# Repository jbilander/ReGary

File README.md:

# Fat ReGary
A drop in replacement PCB for the Fat Gary chip 

This is WORK IN PROGRESS. If you generate gerbers and order PCBs from this source you are doing so completely at your own risk!.

***

***

***

BOM Rev. 1A
---------
Reference  | Name/Value   | Package | Notes
-|-|-|-|
U1 | GW1N-UV1P5LQ100  | TQFP-100_14x14mm_P0.5mm | Gowin FPGA [GW1N-UV1P5LQ100](https://www.mouser.com/ProductDetail/192-GW1P5LQ100C6-I5)
U2 | LM1117-3.3 | SOT-223 | Low-Dropout Linear Regulator 3.3 Volt
U3 | S-1132B43-M5T1U <br />or <br />TPS73643DBVR | SOT-23-5 | Low-Dropout Linear Regulator 4.3 Volt <br /> [S-1132B43-M5T1U](https://www.mouser.com/ProductDetail/628-S-1132B43-M5T1G) <br /> [TPS73643DBVR](https://www.mouser.com/ProductDetail/595-TPS73643DBVR) <br />
U4-U7 | SN74CBT16210 | TSSOP-48 6.1x12.5mm_P0.5mm | 20-BIT FET Bus switch with level shifting, high-speed TTL-compatible. [SN74CBT16210CDGGR ](https://www.mouser.com/ProductDetail/595-SN74CBT16210CDGG)
U8 | Winslow PLCC-84 Plug | PLCC-84 Plug | Optionally use a home made plug (stacked PCBs)
U9 | PLCC-84_TH_pin_holes | TH_plug_pins | Pins that could be used with the DIY-plug PCBs rev1d for manual fitting, L8.7mm [Aliexpress](https://www.aliexpress.com/item/32893608810.html).
R1 | 4.7k Ω | 0603 | Pull-down resistor for TCK (in JTAG)
RN1 | CAY16-103J4LF RES ARRAY 4 Resistors 10k Ω | 1206 | [CAY16-103J4LF](https://www.mouser.com/ProductDetail/652-CAY16-103J4LF)
C1-C3 | Capacitor 10uF | 1206 | 
C4-C6 | Capacitor 1uF | 0805 | 
C7-C12 | Capacitor 0.1uF = 100nF | 0805 | 
C13-C23 | Capacitor 0.01uF = 10nF | 0603 |
JTAG | SMT Pin Header Male | SMT 2 x 3 Pin 2.0mm pitch |

***

When ordering from JLCPCB select:

Specify Layer Sequence: Yes

    L1(Top layer):    F_Cu.gbr
    L2(Inner layer1): GND_Cu.gbr
    L3(Inner layer2): 4V3_Cu.gbr
    L4(Bottom layer): B_Cu.gbr

Remove Order Number: 

    Specify a location

This will notify JLC where to put the order number, they will replace the "JLCJLCJLCJLC" silkscreen label.

***

[![CC BY-SA 4.0][cc-by-sa-shield]][cc-by-sa]

This work is licensed under a
[Creative Commons Attribution-ShareAlike 4.0 International License][cc-by-sa].

[![CC BY-SA 4.0][cc-by-sa-image]][cc-by-sa]

[cc-by-sa]: http://creativecommons.org/licenses/by-sa/4.0/
[cc-by-sa-image]: https://licensebuttons.net/l/by-sa/4.0/88x31.png
[cc-by-sa-shield]: https://img.shields.io/badge/License-CC%20BY--SA%204.0-lightgrey.svg

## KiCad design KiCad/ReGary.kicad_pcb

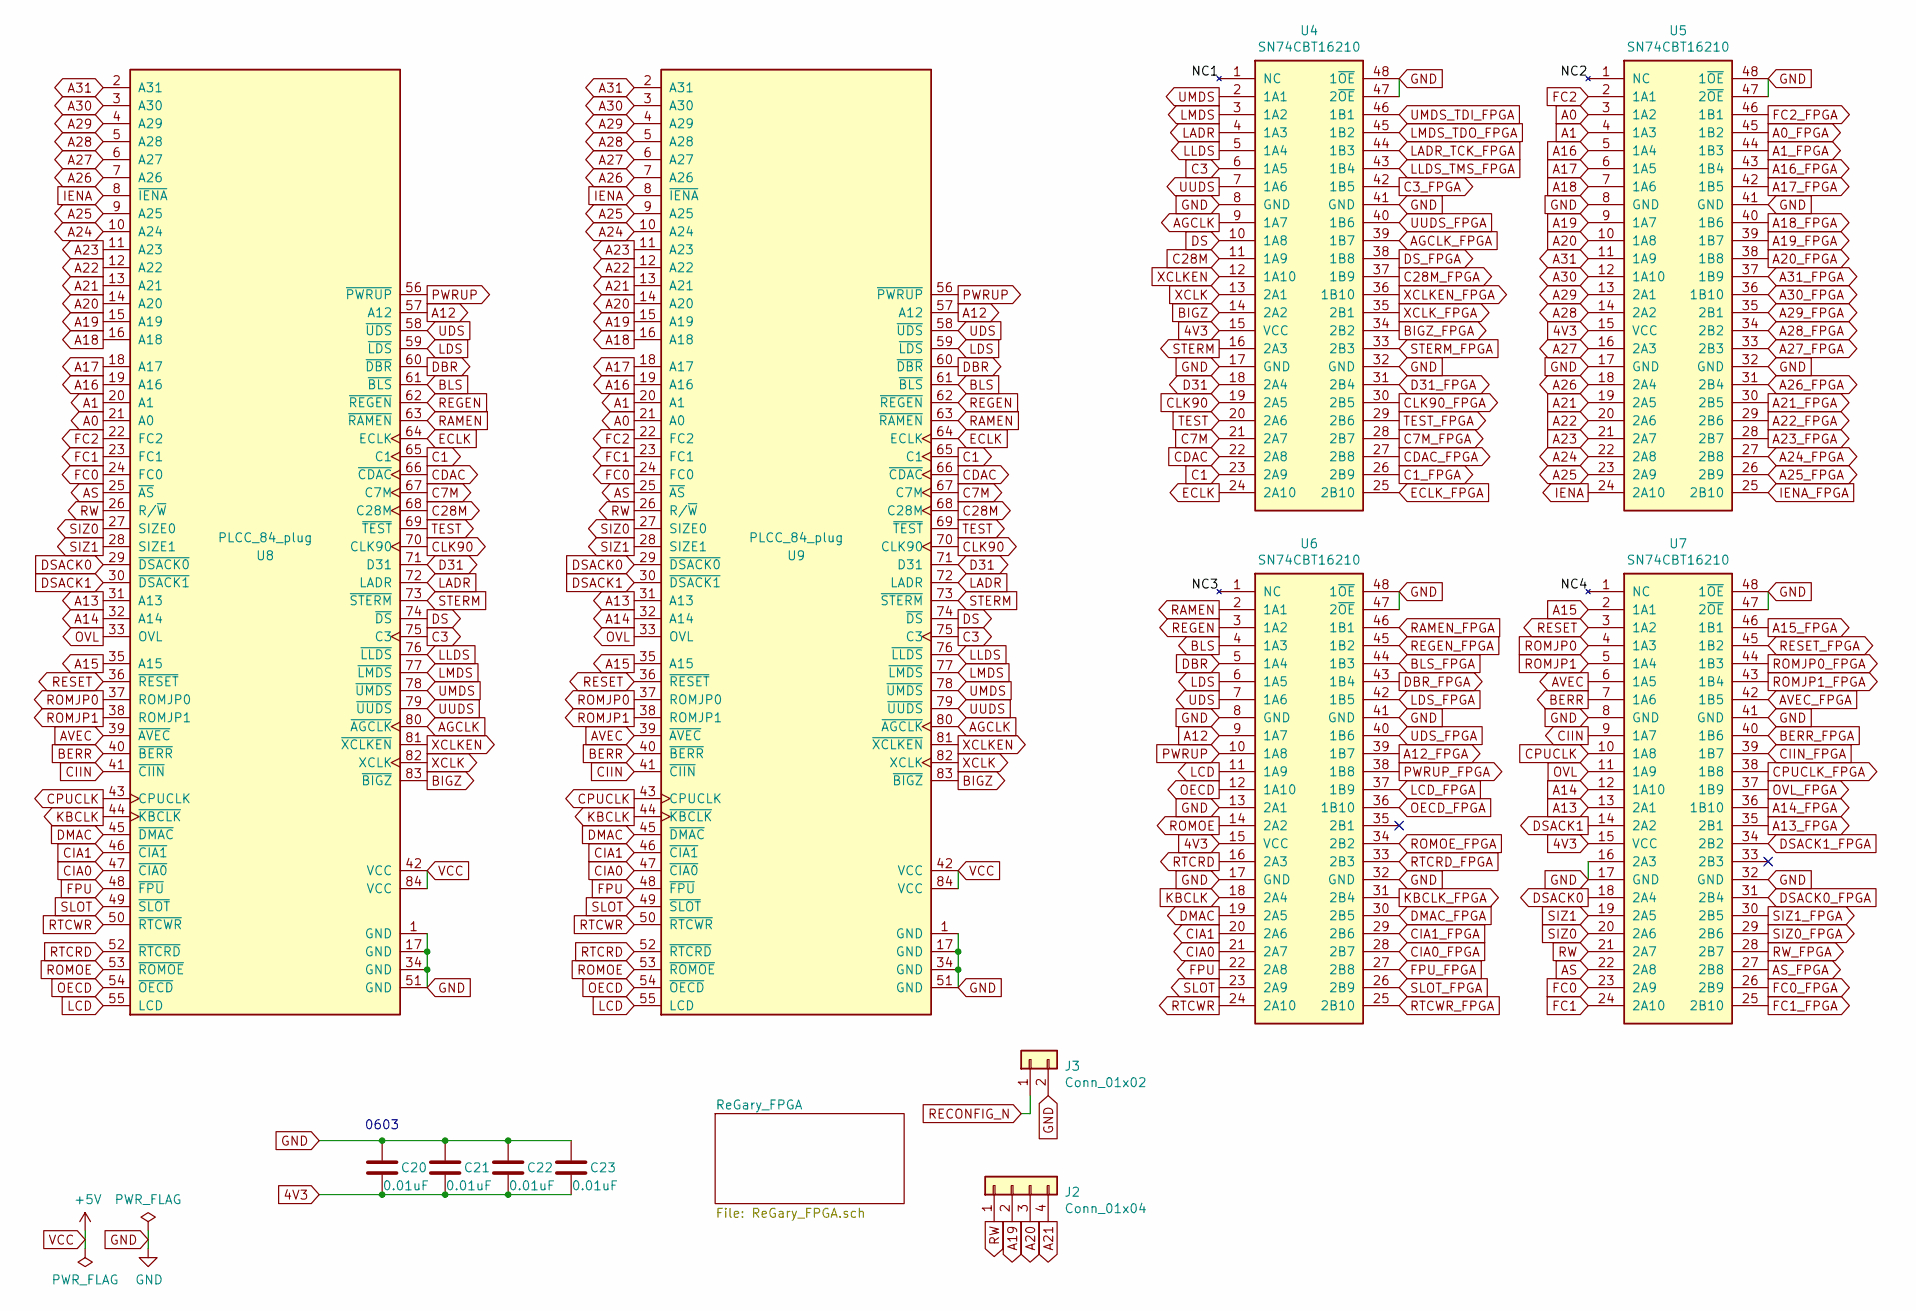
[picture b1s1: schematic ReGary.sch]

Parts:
C20, C21, C22, C23: 0.01uF; C_0603_1608Metric_Pad1.05x0.95mm_HandSolder
J2: Conn_01x04; PinHeader_1x04_P1.27mm_Vertical
J3: Conn_01x02; PinHeader_1x02_P1.27mm_Vertical
U4, U5, U6, U7: SN74CBT16210; TSSOP-48_6.1x12.5mm_P0.5mm_padLength_1mm
U8: PLCC_84_plug; PLCC-84_Plug_P1.27mm_mirrored
U9: PLCC_84_plug; PLCC-84_TH_pin_holes

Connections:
4V3: C20.2, C21.2, C22.2, C23.2, U4.15 (VCC), U5.15 (VCC), U6.15 (VCC), U7.15 (VCC); also elsewhere on the board
/NC1: U4.1 (NC)
/NC2: U5.1 (NC)
/NC3: U6.1 (NC)
/NC4: U7.1 (NC)
A0: U5.3 (1A2), U8.21 (A0), U9.21 (A0)
A0_FPGA: U5.45 (1B2); also elsewhere on the board
A1: U5.4 (1A3), U8.20 (A1), U9.20 (A1)
A1_FPGA: U5.44 (1B3); also elsewhere on the board
A12: U6.9 (1A7), U8.57 (A12), U9.57 (A12)
A12_FPGA: U6.39 (1B7); also elsewhere on the board
A13: U7.13 (2A1), U8.31 (A13), U9.31 (A13)
A13_FPGA: U7.35 (2B1); also elsewhere on the board
A14: U7.12 (1A10), U8.32 (A14), U9.32 (A14)
A14_FPGA: U7.36 (1B10); also elsewhere on the board
A15: U7.2 (1A1), U8.35 (A15), U9.35 (A15)
A15_FPGA: U7.46 (1B1); also elsewhere on the board
A16: U5.5 (1A4), U8.19 (A16), U9.19 (A16)
A16_FPGA: U5.43 (1B4); also elsewhere on the board
A17: U5.6 (1A5), U8.18 (A17), U9.18 (A17)
A17_FPGA: U5.42 (1B5); also elsewhere on the board
A18: U5.7 (1A6), U8.16 (A18), U9.16 (A18)
A18_FPGA: U5.40 (1B6); also elsewhere on the board
A19: J2.2, U5.9 (1A7), U8.15 (A19), U9.15 (A19)
A19_FPGA: U5.39 (1B7); also elsewhere on the board
A20: J2.3, U5.10 (1A8), U8.14 (A20), U9.14 (A20)
A20_FPGA: U5.38 (1B8); also elsewhere on the board
A21: J2.4, U5.19 (2A5), U8.13 (A21), U9.13 (A21)
A21_FPGA: U5.30 (2B5); also elsewhere on the board
A22: U5.20 (2A6), U8.12 (A22), U9.12 (A22)
A22_FPGA: U5.29 (2B6); also elsewhere on the board
A23: U5.21 (2A7), U8.11 (A23), U9.11 (A23)
A23_FPGA: U5.28 (2B7); also elsewhere on the board
A24: U5.22 (2A8), U8.10 (A24), U9.10 (A24)
A24_FPGA: U5.27 (2B8); also elsewhere on the board
A25: U5.23 (2A9), U8.9 (A25), U9.9 (A25)
A25_FPGA: U5.26 (2B9); also elsewhere on the board
A26: U5.18 (2A4), U8.7 (A26), U9.7 (A26)
A26_FPGA: U5.31 (2B4); also elsewhere on the board
A27: U5.16 (2A3), U8.6 (A27), U9.6 (A27)
A27_FPGA: U5.33 (2B3); also elsewhere on the board
A28: U5.14 (2A2), U8.5 (A28), U9.5 (A28)
A28_FPGA: U5.34 (2B2); also elsewhere on the board
A29: U5.13 (2A1), U8.4 (A29), U9.4 (A29)
A29_FPGA: U5.35 (2B1); also elsewhere on the board
A30: U5.12 (1A10), U8.3 (A30), U9.3 (A30)
A30_FPGA: U5.36 (1B10); also elsewhere on the board
A31: U5.11 (1A9), U8.2 (A31), U9.2 (A31)
A31_FPGA: U5.37 (1B9); also elsewhere on the board
AGCLK: U4.9 (1A7), U8.80 (~AGCLK), U9.80 (~AGCLK)
AGCLK_FPGA: U4.39 (1B7); also elsewhere on the board
AS: U7.22 (2A8), U8.25 (~AS), U9.25 (~AS)
AS_FPGA: U7.27 (2B8); also elsewhere on the board
AVEC: U7.6 (1A5), U8.39 (~AVEC), U9.39 (~AVEC)
AVEC_FPGA: U7.42 (1B5); also elsewhere on the board
BERR: U7.7 (1A6), U8.40 (~BERR), U9.40 (~BERR)
BERR_FPGA: U7.40 (1B6); also elsewhere on the board
BIGZ: U4.14 (2A2), U8.83 (~BIGZ), U9.83 (~BIGZ)
BIGZ_FPGA: U4.34 (2B2); also elsewhere on the board
BLS: U6.4 (1A3), U8.61 (~BLS), U9.61 (~BLS)
BLS_FPGA: U6.44 (1B3); also elsewhere on the board
C1: U4.23 (2A9), U8.65 (C1), U9.65 (C1)
C1_FPGA: U4.26 (2B9); also elsewhere on the board
C3: U4.6 (1A5), U8.75 (C3), U9.75 (C3)
C3_FPGA: U4.42 (1B5); also elsewhere on the board
C7M: U4.21 (2A7), U8.67 (C7M), U9.67 (C7M)
C7M_FPGA: U4.28 (2B7); also elsewhere on the board
C28M: U4.11 (1A9), U8.68 (C28M), U9.68 (C28M)
C28M_FPGA: U4.37 (1B9); also elsewhere on the board
CDAC: U4.22 (2A8), U8.66 (~CDAC), U9.66 (~CDAC)
CDAC_FPGA: U4.27 (2B8); also elsewhere on the board
CIA0: U6.21 (2A7), U8.47 (~CIA0), U9.47 (~CIA0)
CIA0_FPGA: U6.28 (2B7); also elsewhere on the board
CIA1: U6.20 (2A6), U8.46 (~CIA1), U9.46 (~CIA1)
CIA1_FPGA: U6.29 (2B6); also elsewhere on the board
CIIN: U7.9 (1A7), U8.41 (~CIIN), U9.41 (~CIIN)
CIIN_FPGA: U7.39 (1B7); also elsewhere on the board
CLK90: U4.19 (2A5), U8.70 (CLK90), U9.70 (CLK90)
CLK90_FPGA: U4.30 (2B5); also elsewhere on the board
CPUCLK: U7.10 (1A8), U8.43 (CPUCLK), U9.43 (CPUCLK)
CPUCLK_FPGA: U7.38 (1B8); also elsewhere on the board
D31: U4.18 (2A4), U8.71 (D31), U9.71 (D31)
D31_FPGA: U4.31 (2B4); also elsewhere on the board
DBR: U6.5 (1A4), U8.60 (~DBR), U9.60 (~DBR)
DBR_FPGA: U6.43 (1B4); also elsewhere on the board
DMAC: U6.19 (2A5), U8.45 (~DMAC), U9.45 (~DMAC)
DMAC_FPGA: U6.30 (2B5); also elsewhere on the board
DS: U4.10 (1A8), U8.74 (~DS), U9.74 (~DS)
DSACK0: U7.18 (2A4), U8.29 (~DSACK0), U9.29 (~DSACK0)
DSACK0_FPGA: U7.31 (2B4); also elsewhere on the board
DSACK1: U7.14 (2A2), U8.30 (~DSACK1), U9.30 (~DSACK1)
DSACK1_FPGA: U7.34 (2B2); also elsewhere on the board
DS_FPGA: U4.38 (1B8); also elsewhere on the board
ECLK: U4.24 (2A10), U8.64 (ECLK), U9.64 (ECLK)
ECLK_FPGA: U4.25 (2B10); also elsewhere on the board
FC0: U7.23 (2A9), U8.24 (FC0), U9.24 (FC0)
FC0_FPGA: U7.26 (2B9); also elsewhere on the board
FC1: U7.24 (2A10), U8.23 (FC1), U9.23 (FC1)
FC1_FPGA: U7.25 (2B10); also elsewhere on the board
FC2: U5.2 (1A1), U8.22 (FC2), U9.22 (FC2)
FC2_FPGA: U5.46 (1B1); also elsewhere on the board
FPU: U6.22 (2A8), U8.48 (~FPU), U9.48 (~FPU)
FPU_FPGA: U6.27 (2B8); also elsewhere on the board
GND: C20.1, C21.1, C22.1, C23.1, J3.2, U4.8 (GND), U4.17 (GND), U4.32 (GND), U4.41 (GND), U4.47 (2~OE), U4.48 (1~OE), U5.8 (GND), U5.17 (GND), U5.32 (GND), U5.41 (GND), U5.47 (2~OE), U5.48 (1~OE), U6.8 (GND), U6.13 (2A1), U6.17 (GND), U6.32 (GND), U6.41 (GND), U6.47 (2~OE), U6.48 (1~OE), U7.8 (GND), U7.16 (2A3), U7.17 (GND), U7.32 (GND), U7.41 (GND), U7.47 (2~OE), U7.48 (1~OE), U8.1 (GND), U8.17 (GND), U8.34 (GND), U8.51 (GND), U9.1 (GND), U9.17 (GND), U9.34 (GND), U9.51 (GND); also elsewhere on the board
IENA: U5.24 (2A10), U8.8 (~IENA), U9.8 (~IENA)
IENA_FPGA: U5.25 (2B10); also elsewhere on the board
KBCLK: U6.18 (2A4), U8.44 (~KBCLK), U9.44 (~KBCLK)
KBCLK_FPGA: U6.31 (2B4); also elsewhere on the board
LADR: U4.4 (1A3), U8.72 (LADR), U9.72 (LADR)
LADR_TCK_FPGA: U4.44 (1B3); also elsewhere on the board
LCD: U6.11 (1A9), U8.55 (LCD), U9.55 (LCD)
LCD_FPGA: U6.37 (1B9); also elsewhere on the board
LDS: U6.6 (1A5), U8.59 (~LDS), U9.59 (~LDS)
LDS_FPGA: U6.42 (1B5); also elsewhere on the board
LLDS: U4.5 (1A4), U8.76 (~LLDS), U9.76 (~LLDS)
LLDS_TMS_FPGA: U4.43 (1B4); also elsewhere on the board
LMDS: U4.3 (1A2), U8.77 (~LMDS), U9.77 (~LMDS)
LMDS_TDO_FPGA: U4.45 (1B2); also elsewhere on the board
OECD: U6.12 (1A10), U8.54 (~OECD), U9.54 (~OECD)
OECD_FPGA: U6.36 (1B10); also elsewhere on the board
OVL: U7.11 (1A9), U8.33 (OVL), U9.33 (OVL)
OVL_FPGA: U7.37 (1B9); also elsewhere on the board
PWRUP: U6.10 (1A8), U8.56 (~PWRUP), U9.56 (~PWRUP)
PWRUP_FPGA: U6.38 (1B8); also elsewhere on the board
RAMEN: U6.2 (1A1), U8.63 (~RAMEN), U9.63 (~RAMEN)
RAMEN_FPGA: U6.46 (1B1); also elsewhere on the board
RECONFIG_N: J3.1; also elsewhere on the board
REGEN: U6.3 (1A2), U8.62 (~REGEN), U9.62 (~REGEN)
REGEN_FPGA: U6.45 (1B2); also elsewhere on the board
RESET: U7.3 (1A2), U8.36 (~RESET), U9.36 (~RESET)
RESET_FPGA: U7.45 (1B2); also elsewhere on the board
ROMJP0: U7.4 (1A3), U8.37 (ROMJP0), U9.37 (ROMJP0)
ROMJP0_FPGA: U7.44 (1B3); also elsewhere on the board
ROMJP1: U7.5 (1A4), U8.38 (ROMJP1), U9.38 (ROMJP1)
ROMJP1_FPGA: U7.43 (1B4); also elsewhere on the board
ROMOE: U6.14 (2A2), U8.53 (~ROMOE), U9.53 (~ROMOE)
ROMOE_FPGA: U6.34 (2B2); also elsewhere on the board
RTCRD: U6.16 (2A3), U8.52 (~RTCRD), U9.52 (~RTCRD)
RTCRD_FPGA: U6.33 (2B3); also elsewhere on the board
RTCWR: U6.24 (2A10), U8.50 (~RTCWR), U9.50 (~RTCWR)
RTCWR_FPGA: U6.25 (2B10); also elsewhere on the board
RW: J2.1, U7.21 (2A7), U8.26 (R/~W), U9.26 (R/~W)
RW_FPGA: U7.28 (2B7); also elsewhere on the board
SIZ0: U7.20 (2A6), U8.27 (SIZE0), U9.27 (SIZE0)
SIZ0_FPGA: U7.29 (2B6); also elsewhere on the board
SIZ1: U7.19 (2A5), U8.28 (SIZE1), U9.28 (SIZE1)
SIZ1_FPGA: U7.30 (2B5); also elsewhere on the board
SLOT: U6.23 (2A9), U8.49 (~SLOT), U9.49 (~SLOT)
SLOT_FPGA: U6.26 (2B9); also elsewhere on the board
STERM: U4.16 (2A3), U8.73 (~STERM), U9.73 (~STERM)
STERM_FPGA: U4.33 (2B3); also elsewhere on the board
TEST: U4.20 (2A6), U8.69 (~TEST), U9.69 (~TEST)
TEST_FPGA: U4.29 (2B6); also elsewhere on the board
UDS: U6.7 (1A6), U8.58 (~UDS), U9.58 (~UDS)
UDS_FPGA: U6.40 (1B6); also elsewhere on the board
UMDS: U4.2 (1A1), U8.78 (~UMDS), U9.78 (~UMDS)
UMDS_TDI_FPGA: U4.46 (1B1); also elsewhere on the board
UUDS: U4.7 (1A6), U8.79 (~UUDS), U9.79 (~UUDS)
UUDS_FPGA: U4.40 (1B6); also elsewhere on the board
VCC: U8.42 (VCC), U8.84 (VCC), U9.42 (VCC), U9.84 (VCC); also elsewhere on the board
XCLK: U4.13 (2A1), U8.82 (XCLK), U9.82 (XCLK)
XCLKEN: U4.12 (1A10), U8.81 (~XCLKEN), U9.81 (~XCLKEN)
XCLKEN_FPGA: U4.36 (1B10); also elsewhere on the board
XCLK_FPGA: U4.35 (2B1); also elsewhere on the board

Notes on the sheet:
0603

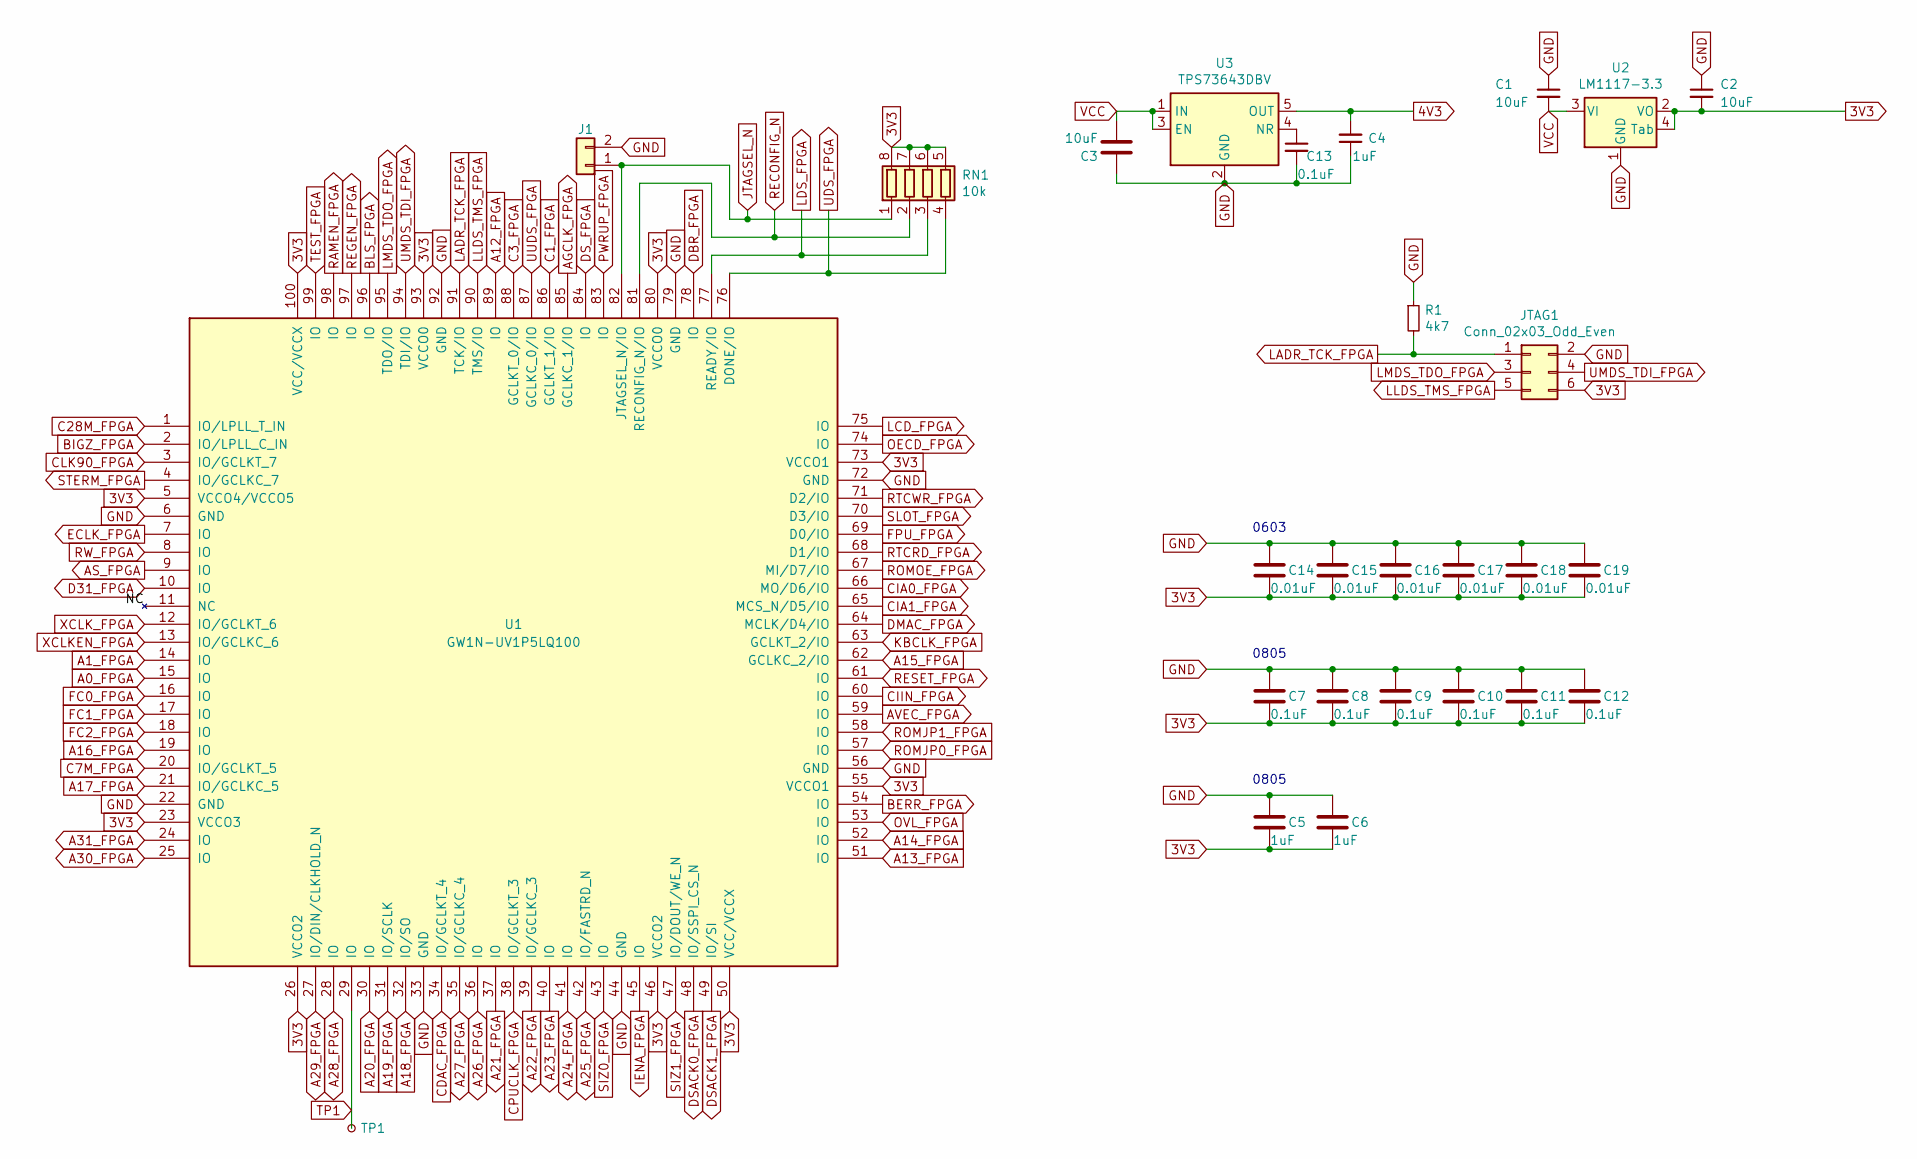
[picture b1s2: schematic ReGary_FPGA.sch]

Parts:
C1, C2, C3: 10uF; C_1206_3216Metric_Pad1.42x1.75mm_HandSolder
C4: 1uF; C_0805_2012Metric_Pad1.15x1.40mm_HandSolder
C5, C6: 1uF; C_0805_2012Metric_Pad1.18x1.45mm_HandSolder
C7, C8, C9, C10, C11, C12: 0.1uF; C_0805_2012Metric_Pad1.18x1.45mm_HandSolder
C13: 0.1uF; C_0603_1608Metric_Pad1.08x0.95mm_HandSolder
C14, C15, C16, C17, C18, C19: 0.01uF; C_0603_1608Metric_Pad1.08x0.95mm_HandSolder
J1: Conn_01x02; PinHeader_1x02_P2.54mm_Vertical
JTAG1: Conn_02x03_Odd_Even; PinHeader_2x03_P2.00mm_Vertical_SMD
R1: 4k7; R_0603_1608Metric_Pad0.98x0.95mm_HandSolder
RN1: 10k; RESCAF80P320X160X60-8N
TP1: TestPoint_Small; TestPoint_Pad_1.5x1.5mm
U1: GW1N-UV1P5LQ100; TQFP-100_14x14mm_P0.5mm
U2: LM1117-3.3; SOT-223
U3: TPS73643DBV; SOT-23-5

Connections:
3V3: C2.2, C5.2, C6.2, C7.2, C8.2, C9.2, C10.2, C11.2, C12.2, C14.2, C15.2, C16.2, C17.2, C18.2, C19.2, JTAG1.6, RN1.5 (R4.2), RN1.6 (R3.2), RN1.7 (R2.2), RN1.8 (R1.2), U1.5 (VCCO4/VCCO5), U1.23 (VCCO3), U1.26 (VCCO2), U1.46 (VCCO2), U1.50 (VCC/VCCX), U1.55 (VCCO1), U1.73 (VCCO1), U1.80 (VCCO0), U1.93 (VCCO0), U1.100 (VCC/VCCX), U2.2 (VO), U2.4 (Tab)
4V3: C4.2, U3.5 (OUT); also elsewhere on the board
/ReGary_FPGA/NC: U1.11 (NC)
A0_FPGA: U1.15 (IO); also elsewhere on the board
A1_FPGA: U1.14 (IO); also elsewhere on the board
A12_FPGA: U1.89 (IO); also elsewhere on the board
A13_FPGA: U1.51 (IO); also elsewhere on the board
A14_FPGA: U1.52 (IO); also elsewhere on the board
A15_FPGA: U1.62 (GCLKC_2/IO); also elsewhere on the board
A16_FPGA: U1.19 (IO); also elsewhere on the board
A17_FPGA: U1.21 (IO/GCLKC_5); also elsewhere on the board
A18_FPGA: U1.32 (IO/SO); also elsewhere on the board
A19_FPGA: U1.31 (IO/SCLK); also elsewhere on the board
A20_FPGA: U1.30 (IO); also elsewhere on the board
A21_FPGA: U1.37 (IO); also elsewhere on the board
A22_FPGA: U1.39 (IO/GCLKC_3); also elsewhere on the board
A23_FPGA: U1.40 (IO); also elsewhere on the board
A24_FPGA: U1.41 (IO); also elsewhere on the board
A25_FPGA: U1.42 (IO/FASTRD_N); also elsewhere on the board
A26_FPGA: U1.36 (IO); also elsewhere on the board
A27_FPGA: U1.35 (IO/GCLKC_4); also elsewhere on the board
A28_FPGA: U1.28 (IO); also elsewhere on the board
A29_FPGA: U1.27 (IO/DIN/CLKHOLD_N); also elsewhere on the board
A30_FPGA: U1.25 (IO); also elsewhere on the board
A31_FPGA: U1.24 (IO); also elsewhere on the board
AGCLK_FPGA: U1.85 (GCLKC_1/IO); also elsewhere on the board
AS_FPGA: U1.9 (IO); also elsewhere on the board
AVEC_FPGA: U1.59 (IO); also elsewhere on the board
BERR_FPGA: U1.54 (IO); also elsewhere on the board
BIGZ_FPGA: U1.2 (IO/LPLL_C_IN); also elsewhere on the board
BLS_FPGA: U1.96 (IO); also elsewhere on the board
C1_FPGA: U1.86 (GCLKT_1/IO); also elsewhere on the board
C3_FPGA: U1.88 (GCLKT_0/IO); also elsewhere on the board
C7M_FPGA: U1.20 (IO/GCLKT_5); also elsewhere on the board
C28M_FPGA: U1.1 (IO/LPLL_T_IN); also elsewhere on the board
CDAC_FPGA: U1.34 (IO/GCLKT_4); also elsewhere on the board
CIA0_FPGA: U1.66 (MO/D6/IO); also elsewhere on the board
CIA1_FPGA: U1.65 (MCS_N/D5/IO); also elsewhere on the board
CIIN_FPGA: U1.60 (IO); also elsewhere on the board
CLK90_FPGA: U1.3 (IO/GCLKT_7); also elsewhere on the board
CPUCLK_FPGA: U1.38 (IO/GCLKT_3); also elsewhere on the board
D31_FPGA: U1.10 (IO); also elsewhere on the board
DBR_FPGA: U1.78 (IO); also elsewhere on the board
DMAC_FPGA: U1.64 (MCLK/D4/IO); also elsewhere on the board
DSACK0_FPGA: U1.48 (IO/SSPI_CS_N); also elsewhere on the board
DSACK1_FPGA: U1.49 (IO/SI); also elsewhere on the board
DS_FPGA: U1.84 (IO); also elsewhere on the board
ECLK_FPGA: U1.7 (IO); also elsewhere on the board
FC0_FPGA: U1.16 (IO); also elsewhere on the board
FC1_FPGA: U1.17 (IO); also elsewhere on the board
FC2_FPGA: U1.18 (IO); also elsewhere on the board
FPU_FPGA: U1.69 (D0/IO); also elsewhere on the board
GND: C1.1, C2.1, C3.1, C4.1, C5.1, C6.1, C7.1, C8.1, C9.1, C10.1, C11.1, C12.1, C13.2, C14.1, C15.1, C16.1, C17.1, C18.1, C19.1, J1.2, JTAG1.2, R1.1, U1.6 (GND), U1.22 (GND), U1.33 (GND), U1.44 (GND), U1.56 (GND), U1.72 (GND), U1.79 (GND), U1.92 (GND), U2.1 (GND), U3.2 (GND); also elsewhere on the board
IENA_FPGA: U1.45 (IO); also elsewhere on the board
JTAGSEL_N: J1.1, RN1.1 (R1.1), U1.82 (JTAGSEL_N/IO)
KBCLK_FPGA: U1.63 (GCLKT_2/IO); also elsewhere on the board
LADR_TCK_FPGA: JTAG1.1, R1.2, U1.91 (TCK/IO); also elsewhere on the board
LCD_FPGA: U1.75 (IO); also elsewhere on the board
LDS_FPGA: RN1.3 (R3.1), U1.77 (READY/IO); also elsewhere on the board
LLDS_TMS_FPGA: JTAG1.5, U1.90 (TMS/IO); also elsewhere on the board
LMDS_TDO_FPGA: JTAG1.3, U1.95 (TDO/IO); also elsewhere on the board
unnamed: C13.1, U3.4 (NR)
OECD_FPGA: U1.74 (IO); also elsewhere on the board
OVL_FPGA: U1.53 (IO); also elsewhere on the board
PWRUP_FPGA: U1.83 (IO); also elsewhere on the board
RAMEN_FPGA: U1.98 (IO); also elsewhere on the board
RECONFIG_N: RN1.2 (R2.1), U1.81 (RECONFIG_N/IO); also elsewhere on the board
REGEN_FPGA: U1.97 (IO); also elsewhere on the board
RESET_FPGA: U1.61 (IO); also elsewhere on the board
ROMJP0_FPGA: U1.57 (IO); also elsewhere on the board
ROMJP1_FPGA: U1.58 (IO); also elsewhere on the board
ROMOE_FPGA: U1.67 (MI/D7/IO); also elsewhere on the board
RTCRD_FPGA: U1.68 (D1/IO); also elsewhere on the board
RTCWR_FPGA: U1.71 (D2/IO); also elsewhere on the board
RW_FPGA: U1.8 (IO); also elsewhere on the board
SIZ0_FPGA: U1.43 (IO); also elsewhere on the board
SIZ1_FPGA: U1.47 (IO/DOUT/WE_N); also elsewhere on the board
SLOT_FPGA: U1.70 (D3/IO); also elsewhere on the board
STERM_FPGA: U1.4 (IO/GCLKC_7); also elsewhere on the board
TEST_FPGA: U1.99 (IO); also elsewhere on the board
TP1: TP1.1, U1.29 (IO)
UDS_FPGA: RN1.4 (R4.1), U1.76 (DONE/IO); also elsewhere on the board
UMDS_TDI_FPGA: JTAG1.4, U1.94 (TDI/IO); also elsewhere on the board
UUDS_FPGA: U1.87 (GCLKC_0/IO); also elsewhere on the board
VCC: C1.2, C3.2, U2.3 (VI), U3.1 (IN), U3.3 (EN); also elsewhere on the board
XCLKEN_FPGA: U1.13 (IO/GCLKC_6); also elsewhere on the board
XCLK_FPGA: U1.12 (IO/GCLKT_6); also elsewhere on the board

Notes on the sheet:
0603
0805

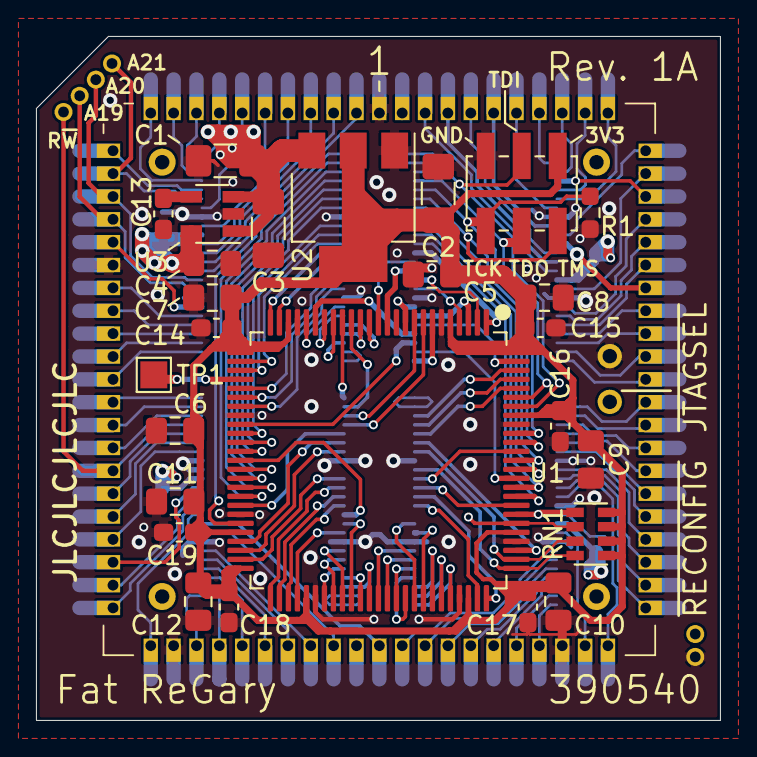
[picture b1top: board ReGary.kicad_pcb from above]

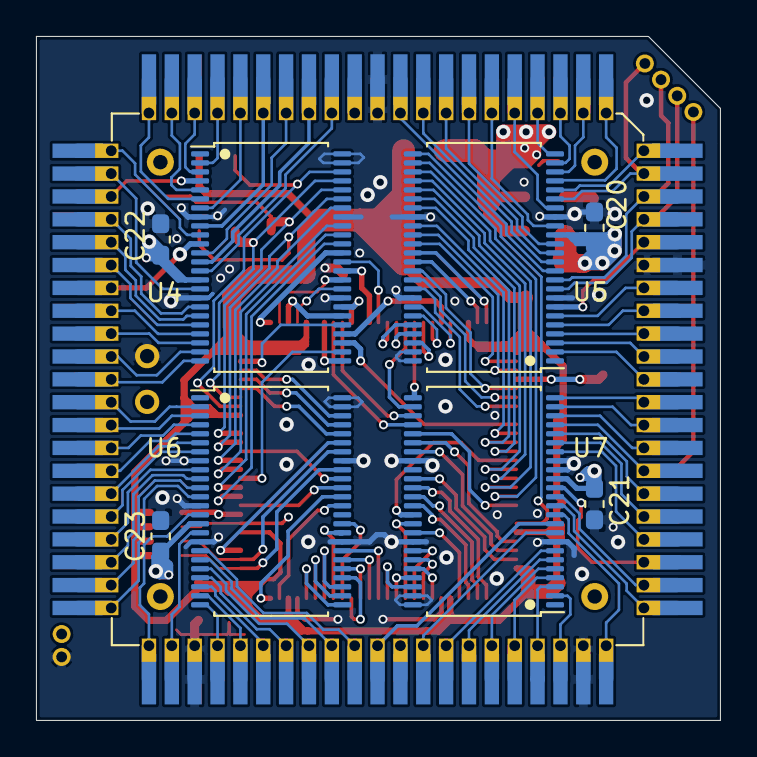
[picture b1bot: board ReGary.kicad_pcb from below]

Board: 4 copper layers, 38.0 x 38.0 mm, 39 parts (9 on the bottom side), 164 nets.

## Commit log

2025-02-12 Updated .gitignore file
2025-02-12 Add license
2025-02-12 Add footprints
2025-02-12 Add 3D-models
2025-02-12 Add KiCad files
2025-02-12 Add Fat Gary socket symbol and change to it
2025-02-12 Removed BGA FPGA
2025-02-12 Add Gowin FPGA GW1N-UV1P5LQ100 into the design
2025-02-12 Add footprint
2025-02-13 Change to 6-pin JTAG-header
2025-02-13 Fix placement of VCC vias, C1 and U2 voltage regulator
2025-02-13 Add a 4V3 LDO voltage regulator
2025-02-14 Change level shifters from CBTD to CBT with 4V3 power supply, change inner power layer from VCC to 4V3
2025-02-14 Fixed placement of C5 and FPGA, more cleanup of old vias and traces
2025-02-14 fixed placement of capacitors C8 and C9
2025-02-15 Add JTAG routing and 4.7k pull-down resistor on TCK-line
2025-02-15 fixed placement of capacitors C9,C10 and resistor array RN1
2025-02-15 Add JP header for JTAGSEL_N, fixed JTAG as dual-purpose pins
2025-02-16 Removed the 0.45 mm / 0.2 mm via option
2025-02-16 More signal to pin assignments and routing
2025-02-16 More FPGA pin assignments and routing
2025-02-17 Placement of caps and more routing
2025-02-18 More signal to pin assignments and routing done, moved /REGEN and /RAMEN signals to FPGA pin 97,98
2025-02-18 More pin assignments and routing
2025-02-18 Placement of caps and more routing of 3V3-power
2025-02-20 More signals to pin assignments and more routing done
2025-02-20 Improved GND by adding/relocating some GND-vias, also more routing fixes done
2025-02-20 Fixed enumeration of capacitors and placement of last capacitor C11 for 3V3-power
2025-02-20 Fixed JTAGSEL_N header size and silkscreen placement
2025-02-20 silkscreen fixes on front side
2025-02-21 silkscreen fixes on the underside
2025-03-02 Add a pin-header (with RW, A21, A20, A19 signals) for a built in Romy
2025-04-22 Add 1.27 mm pitch pin-header for RECONFIG_N signal
2025-05-08 Add schematic pdf
2025-06-14 Add images
